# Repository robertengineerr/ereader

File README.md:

# e-reader

An open-source e-reader built on the ESP32-S3. Bare-metal C++ firmware, web-based book management, physical controls. Designed for FOSS developers to build on top of solid hardware.

## Schematic

The full KiCad project is in [`hardware/e_reader_v0.1/`](hardware/e_reader_v0.1/). Pin reference is in [`hardware/connections.md`](hardware/connections.md).

## Hardware

| Component | Part (PCB rev 0.2.0) |
|---|---|
| MCU | ESP32-S3-WROOM-1-N16R8 (16 MB flash, 8 MB octal PSRAM) |
| Display | Waveshare 7.5" V2 e-ink (800×480) via driver HAT on a 9-pin header |
| Storage | microSD (Molex 104031-0811), SPI, FAT32, card detect |
| Input | Alps SKRHABE010 5-way joystick, plus SET / RST / BOOT / RESET buttons |
| Battery | 1-cell protected LiPo via JST-PH, MCP73831 charger, PTC + reverse-polarity FET |
| Power | USB-C (charging + native USB programming), RT9080 3.3 V LDO (~2 µA Iq), slide switch on LDO enable |

The BOM, with an LCSC number for every assembled part, is in
[`hardware/e_reader_v0.1/e_reader_v0.1_bom.csv`](hardware/e_reader_v0.1/e_reader_v0.1_bom.csv).
The design-review log is in [`hardware/REVIEW.md`](hardware/REVIEW.md).

### Wiring

Full pin tables for the breadboard and the PCB are in [`hardware/connections.md`](hardware/connections.md).
The firmware takes its pins from [`src/pins.h`](src/pins.h): the default build uses the breadboard map,
and `pio run -e pcb` uses the PCB map.

The PCB pins that differ from the breadboard are:
| Signal | Breadboard | PCB | Why |
|---|---|---|---|
| Joystick UP / DOWN | GPIO36 / 37 | GPIO4 / 5 | GPIO35–37 are used by the N16R8's octal PSRAM |
| Joystick COM | GPIO35 driven LOW | GND | |
| Display DIN | GPIO46 | GPIO14 | GPIO46 is a boot strapping pin |
| SD card detect | — | GPIO6 | |
| Battery voltage | — | GPIO1 (×2 divider) | |

## Building

1. Install [PlatformIO](https://platformio.org/)
2. Create `src/secrets.h` with your WiFi credentials:
```cpp
#define WIFI_SSID "your-ssid"
#define WIFI_PASS "your-password"
```
3. Build and flash:
```bash
pio run --target upload            # breadboard (DevKitC-1)
pio run -e pcb --target upload     # custom PCB (first time: SW10 ON, hold BOOT, tap RESET; see hardware/connections.md)
```

## Usage

| Button | Library | Reading | Settings |
|---|---|---|---|
| UP | Cursor up | Previous page | Cursor up |
| DOWN | Cursor down | Next page | Cursor down |
| RIGHT | — | Next page | — |
| MID | Select | Back to library | Select |
| LEFT | — | Back to library | Back to library |
| Hold SET at boot | — | — | Enter WiFi mode |

### WiFi Upload

Hold SET while pressing reset, or navigate **Settings → WiFi Upload**. The device connects to your WiFi and shows `ereader.local` on screen. Open `http://ereader.local` in a browser to upload and delete books.

Supported formats (converted to plain text in the browser):
- `.txt` — uploaded directly
- `.epub` — extracted in browser via JSZip
- `.pdf` — extracted via PDF.js
- `.docx` — extracted via JSZip
- `.html` / `.htm` — stripped in browser
- `.fb2` — parsed in browser

Press MID on the device or click **Exit WiFi Mode** in the browser to return to the library.

### Fallback

If no SD card is present the device falls back to a built-in sample text (Iliad Book I, Pope translation) so the UI is always usable.

## Project Structure

```
src/
  main.cpp          # setup, loop, ISR input handling, state machine
  display.cpp/h     # e-ink display abstraction (GxEPD2)
  sd_manager.cpp/h  # SD card init, book listing, pagination engine
  network.cpp/h     # WiFi, HTTP file manager, mDNS
  web_ui.h          # embedded HTML/JS for the browser file manager
  secrets.h         # WiFi credentials (not in repo — create your own)

hardware/
  connections.md              # full pin reference for KiCad
  e_reader_v0.1/              # KiCad project (schematic + PCB)
```

## Roadmap

- [x] Text rendering on e-ink display
- [x] SD card file management
- [x] State machine UI (Library / Reading / Settings)
- [x] WiFi upload with multi-format support
- [x] mDNS (`ereader.local`)
- [x] Hardware schematic v0.1
- [x] Schematic rev 0.2.0: power fixes, 5-way joystick, BOM with LCSC numbers (3 review rounds)
- [x] PCB layout (4-layer, routed, DRC clean) and JLCPCB fab files in `hardware/e_reader_v0.1/fab/`
- [ ] Fabrication and bring-up
- [x] LiPo battery + charging circuit (MCP73831 + RT9080) in schematic
- [ ] Persist reading position (LittleFS)
- [ ] EPUB native rendering
- [ ] 3D printed enclosure

## License

MIT

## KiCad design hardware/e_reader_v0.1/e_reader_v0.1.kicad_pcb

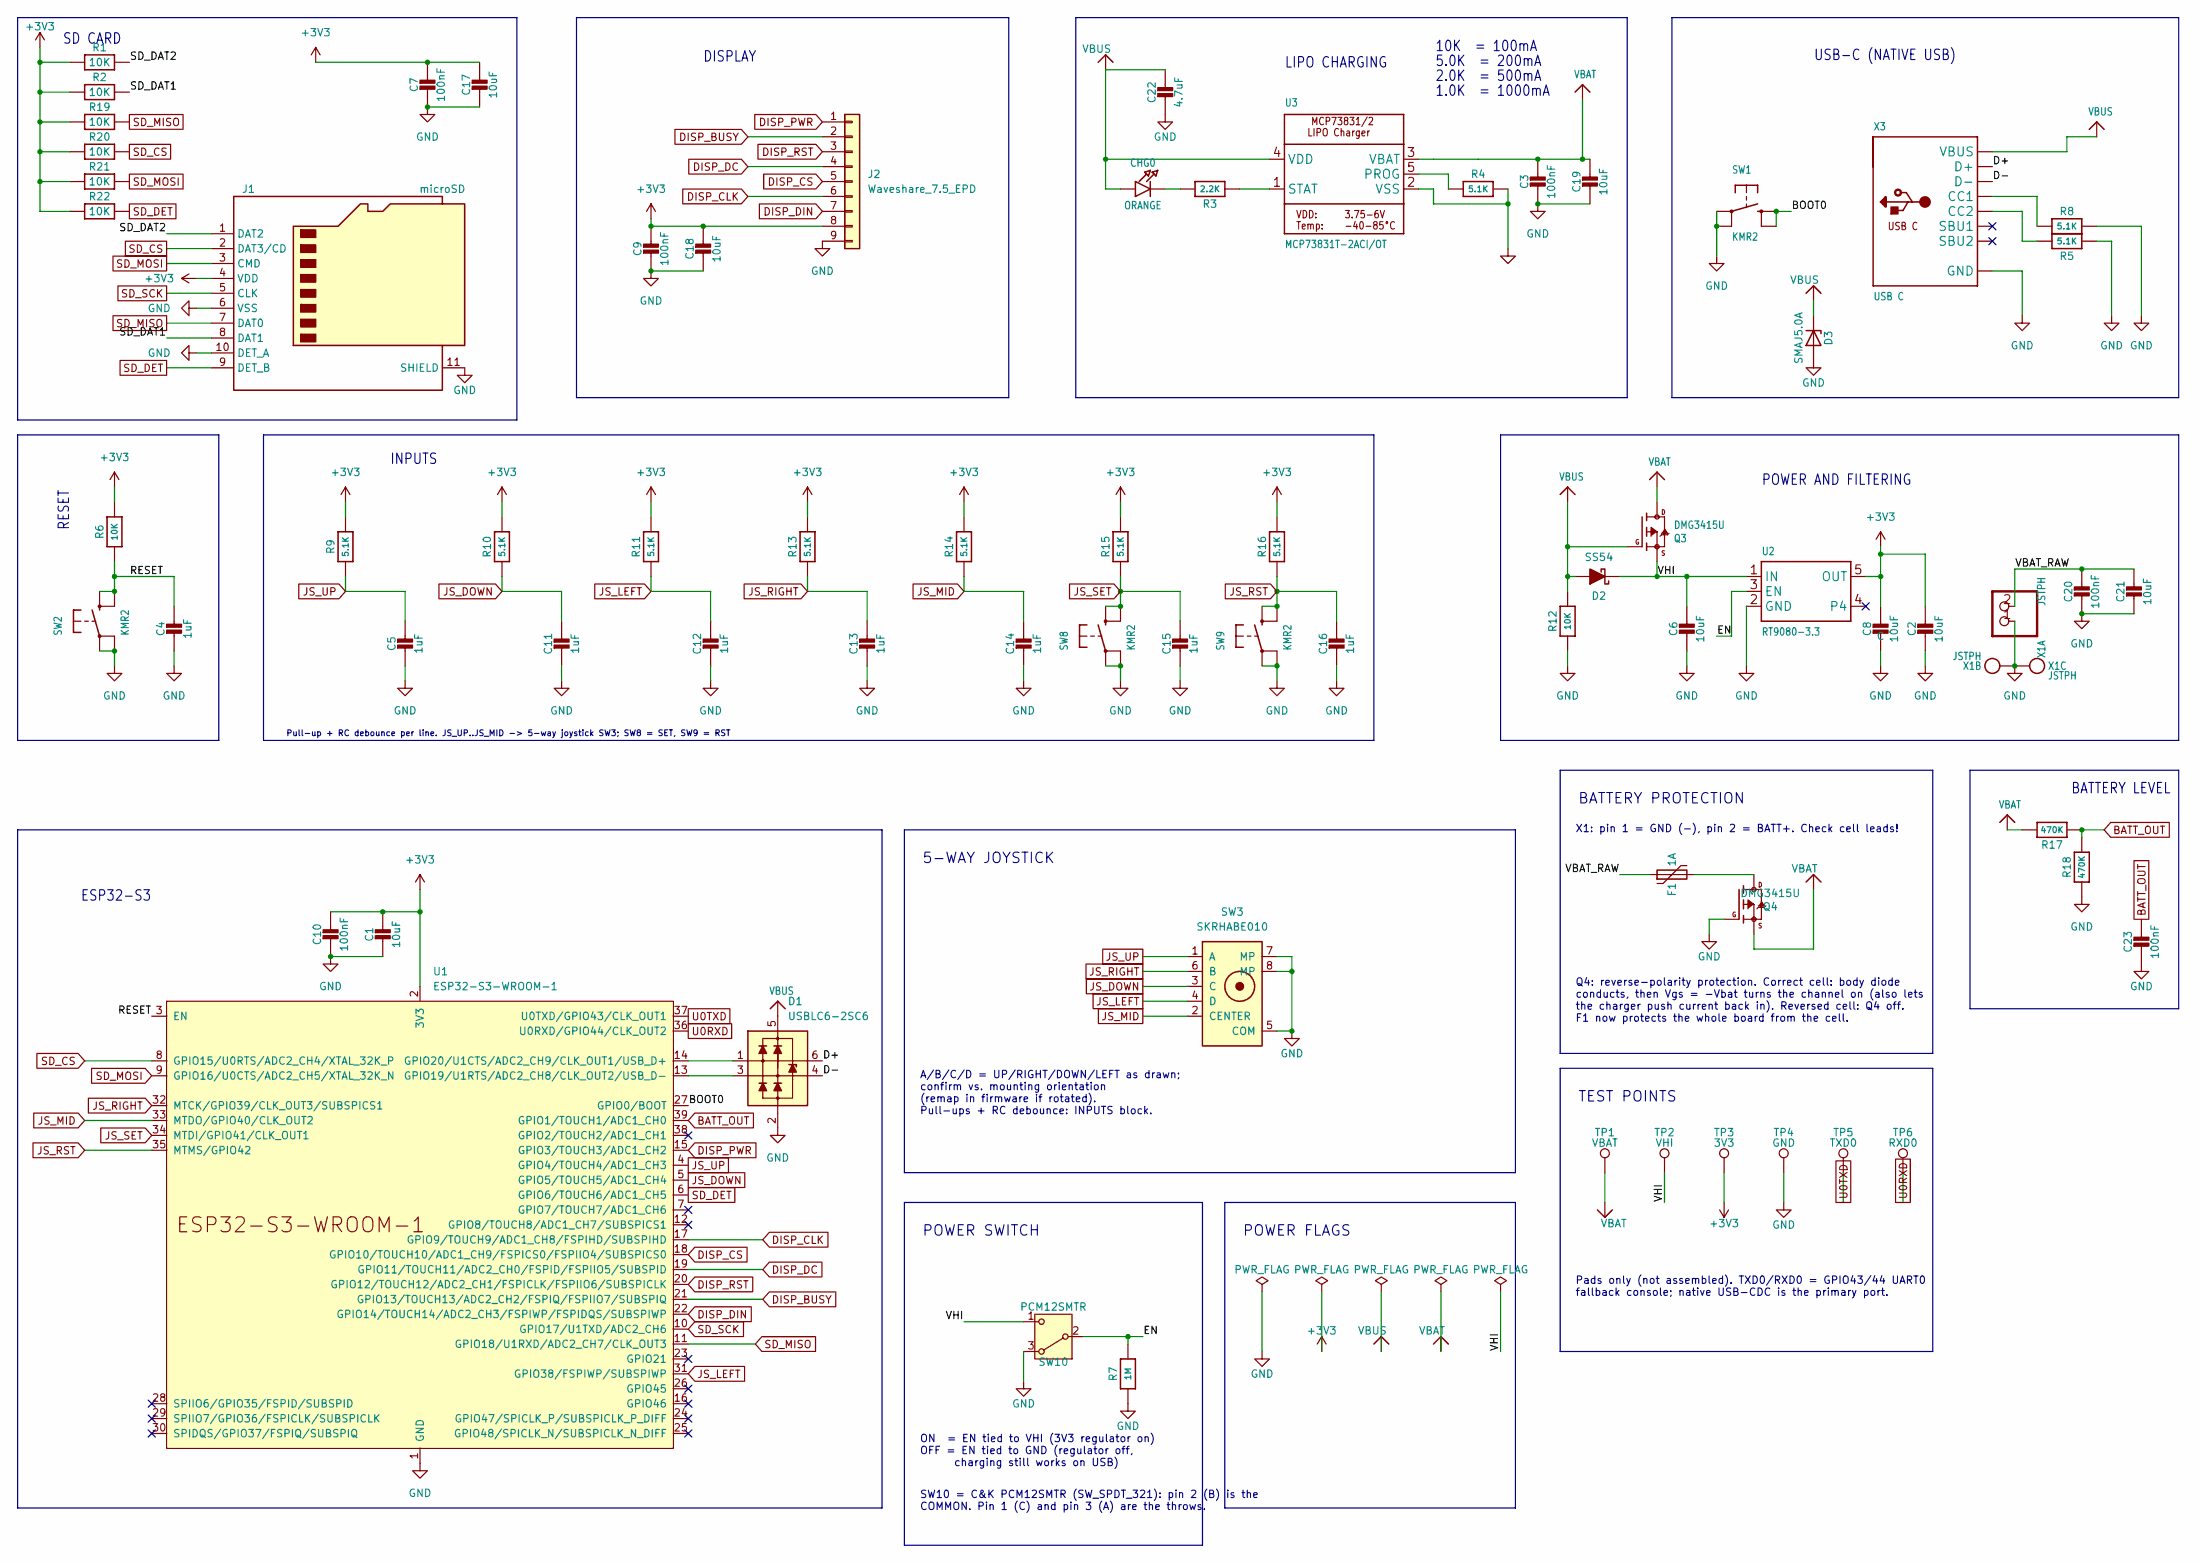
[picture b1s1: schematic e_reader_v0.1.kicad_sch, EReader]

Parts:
C1, C2, C6, C8, C17, C18, C19, C21: 10uF; C_0805_2012Metric; MPN CL21A106KAYNNNE; LCSC C15850
C3, C7, C9, C10, C20, C23: 100nF; C_0402_1005Metric; MPN CL05B104KO5NNNC; LCSC C1525
C4, C5, C11, C12, C13, C14, C15, C16: 1uF; C_0402_1005Metric; MPN CL05A105KA5NQNC; LCSC C52923
C22: 4.7uF; C_0805_2012Metric; MPN CL21A475KAQNNNE; LCSC C1779
CHG0: ORANGE; LED_0603_1608Metric; MPN LITEON LTST-C191KFKT; LCSC C160478
D1: USBLC6-2SC6; SOT-23-6; MPN USBLC6-2SC6; LCSC C7519
D2: SS54; D_SMA; MPN SS54 (SMA); LCSC C22452
D3: SMAJ5.0A; D_SMA; MPN Littelfuse SMAJ5.0A; LCSC C83329
F1: 1A; Fuse_1206_3216Metric; MPN LUTE 1206L100/24NR; LCSC C7542957
J1: microSD; microSD_HC_Molex_104031-0811; MPN Molex 104031-0811; LCSC C585350
J2: Waveshare_7.5_EPD; PinHeader_1x09_P2.54mm_Vertical_SMD_INCP_IPCP254M09PB08S; MPN INCP IPCP254M09PB08S; LCSC C22438433
Q3, Q4: DMG3415U; SOT-23; MPN DMG3415U-7; LCSC C96616
R1, R2, R6, R12, R19, R20, R21, R22: 10K; R_0402_1005Metric; MPN 0402WGF1002TCE; LCSC C25744
R3: 2.2K; R_0402_1005Metric; MPN 0402WGF2201TCE; LCSC C25879
R4, R5, R8, R9, R10, R11, R13, R14, R15, R16: 5.1K; R_0402_1005Metric; MPN 0402WGF5101TCE; LCSC C25905
R7: 1M; R_0402_1005Metric; MPN 0402WGF1004TCE; LCSC C26083
R17, R18: 470K; R_0402_1005Metric; MPN 0402WGF4703TCE; LCSC C25790
SW1, SW2, SW8, SW9: KMR2; SW_Push_1P1T_NO_CK_KMR2; MPN C&K KMR221GLFS; LCSC C72443
SW3: SKRHABE010; SW_Alps_SKRHABE010; MPN Alps SKRHABE010; LCSC C139794
SW10: PCM12SMTR; SW_SPDT_PCM12; MPN C&K PCM12SMTR; LCSC C221841
TP1: VBAT; TestPoint_Pad_D1.5mm
TP2: VHI; TestPoint_Pad_D1.5mm
TP3: 3V3; TestPoint_Pad_D1.5mm
TP4: GND; TestPoint_Pad_D1.5mm
TP5: TXD0; TestPoint_Pad_D1.5mm
TP6: RXD0; TestPoint_Pad_D1.5mm
U1: ESP32-S3-WROOM-1; MPN ESP32-S3-WROOM-1-N16R8; LCSC C2913202
U2: RT9080-3.3; SOT-23-5; MPN RT9080-33GJ5; LCSC C841192
U3: MCP73831T-2ACI/OT; SOT-23-5; MPN MCP73831T-2ACI/OT; LCSC C424093
X1: JSTPH; JST_PH_S2B-PH-SM4-TB_1x02-1MP_P2.00mm_Horizontal; MPN JST S2B-PH-SM4-TB(LF)(SN); LCSC C295747
X3: USB C; USB_C_Receptacle_HRO_TYPE-C-31-M-12; MPN HRO TYPE-C-31-M-12; LCSC C165948

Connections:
+3V3: C1.1, C2.1, C7.1, C8.1, C9.1, C10.1, C17.1, C18.1, J1.4 (VDD), J2.8 (VCC), R1.1, R2.1, R6.2, R9.2, R10.2, R11.2, R13.2, R14.2, R15.2, R16.2, R19.1, R20.1, R21.1, R22.1, TP3.1, U1.2 (3V3), U2.5 (OUT)
/BOOT0: SW1.2 (S), U1.27 (GPIO0/BOOT)
/D+: D1.6 (L1), X3.A6 (D+), X3.B6 (D+)
/D-: D1.4 (L2), X3.A7 (D-), X3.B7 (D-)
/EN: R7.2, SW10.2 (B), U2.3 (EN)
/RESET: C4.1, R6.1, SW2.2 (S), U1.3 (EN)
/SD_DAT1: J1.8 (DAT1), R2.2
/SD_DAT2: J1.1 (DAT2), R1.2
/VBAT_RAW: C20.1, C21.1, F1.1, X1.2
/VHI: C6.1, D2.1 (K), Q3.2 (S), SW10.1 (C), TP2.1, U2.1 (IN)
BATT_OUT: C23.1, R17.1, R18.2, U1.39 (GPIO1/TOUCH1/ADC1_CH0)
DISP_BUSY: J2.2 (BUSY), U1.21 (GPIO13/TOUCH13/ADC2_CH2/FSPIQ/FSPIIO7/S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)
DISP_CLK: J2.6 (CLK), U1.17 (GPIO9/TOUCH9/ADC1_CH8/FSPIHD/SUBSPIHD)
DISP_CS: J2.5 (CS), U1.18 (GPIO10/TOUCH10/ADC1_CH9/FSPICS0/FSPIIO4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)
DISP_DC: J2.4 (DC), U1.19 (GPIO11/TOUCH11/ADC2_CH0/FSPID/FSPIIO5/S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)
DISP_DIN: J2.7 (DIN), U1.22 (GPIO14/TOUCH14/ADC2_CH3/FSPIWP/FSPIDQS/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)
DISP_PWR: J2.1 (PWR), U1.15 (GPIO3/TOUCH3/ADC1_CH2)
DISP_RST: J2.3 (RST), U1.20 (GPIO12/TOUCH12/ADC2_CH1/FSPICLK/FSPIIO6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)
GND: C1.2, C2.2, C3.2, C4.2, C5.2, C6.2, C7.2, C8.2, C9.2, C10.2, C11.2, C12.2, C13.2, C14.2, C15.2, C16.2, C17.2, C18.2, C19.2, C20.2, C21.2, C22.2, C23.2, D1.2 (VN), D3.2 (A), J1.6 (VSS), J1.10 (DET_A), J1.11 (SHIELD), J2.9 (GND), Q4.1 (G), R4.2, R5.1, R7.1, R8.2, R12.1, R18.1, SW1.1, SW2.1, SW3.5 (COM), SW3.7 (MP), SW3.8 (MP), SW8.1, SW9.1, SW10.3 (A), TP4.1, U1.1 (GND), U1.40 (GND), U1.41 (GND), U2.2 (GND), U3.2 (VSS), X1.1, X1.MP, X3.A1 (GND), X3.A12 (GND), X3.B1 (GND), X3.B12 (GND), X3.S1 (GND)
JS_DOWN: C11.1, R10.1, SW3.3 (C), U1.5 (GPIO5/TOUCH5/ADC1_CH4)
JS_LEFT: C12.1, R11.1, SW3.4 (D), U1.31 (GPIO38/FSPIWP/SUBSPIWP)
JS_MID: C14.1, R14.1, SW3.2 (CENTER), U1.33 (MTDO/GPIO40/CLK_OUT2)
JS_RIGHT: C13.1, R13.1, SW3.6 (B), U1.32 (MTCK/GPIO39/CLK_OUT3/SUBSPICS1)
JS_RST: C16.1, R16.1, SW9.2 (S), U1.35 (MTMS/GPIO42)
JS_SET: C15.1, R15.1, SW8.2 (S), U1.34 (MTDI/GPIO41/CLK_OUT1)
JS_UP: C5.1, R9.1, SW3.1 (A), U1.4 (GPIO4/TOUCH4/ADC1_CH3)
unnamed: CHG0.1 (C), R3.2
unnamed: F1.2, Q4.3 (D)
unnamed: D1.3 (L2), U1.13 (GPIO19/U1RTS/ADC2_CH8/CLK_OUT2/USB_D-)
unnamed: D1.1 (L1), U1.14 (GPIO20/U1CTS/ADC2_CH9/CLK_OUT1/USB_D+)
unnamed: R4.1, U3.5 (PROG)
unnamed: R3.1, U3.1 (STAT)
unnamed: R8.1, X3.A5 (CC1)
unnamed: R5.2, X3.B5 (CC2)
SD_CS: J1.2 (DAT3/CD), R20.2, U1.8 (GPIO15/U0RTS/ADC2_CH4/XTAL_32K_P)
SD_DET: J1.9 (DET_B), R22.2, U1.6 (GPIO6/TOUCH6/ADC1_CH5)
SD_MISO: J1.7 (DAT0), R19.2, U1.11 (GPIO18/U1RXD/ADC2_CH7/CLK_OUT3)
SD_MOSI: J1.3 (CMD), R21.2, U1.9 (GPIO16/U0CTS/ADC2_CH5/XTAL_32K_N)
SD_SCK: J1.5 (CLK), U1.10 (GPIO17/U1TXD/ADC2_CH6)
U0RXD: TP6.1, U1.36 (U0RXD/GPIO44/CLK_OUT2)
U0TXD: TP5.1, U1.37 (U0TXD/GPIO43/CLK_OUT1)
VBAT: C3.1, C19.1, Q3.3 (D), Q4.2 (S), R17.2, TP1.1, U3.3 (VBAT)
VBUS: C22.1, CHG0.2 (A), D1.5 (VP), D2.2 (A), D3.1 (K), Q3.1 (G), R12.2, U3.4 (VDD), X3.A4 (VBUS), X3.A9 (VBUS), X3.B4 (VBUS), X3.B9 (VBUS)

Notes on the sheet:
INPUTS
LIPO CHARGING
5.0K = 200mA
ESP32-S3
USB-C (NATIVE USB)
RESET
SD CARD
1.0K = 1000mA
10K = 100mA
DISPLAY
2.0K = 500mA
POWER AND FILTERING
BATTERY LEVEL
POWER SWITCH
ON = EN tied to VHI (3V3 regulator on) OFF = EN tied to GND (regulator off, charging still works on USB)
5-WAY JOYSTICK
A/B/C/D = UP/RIGHT/DOWN/LEFT as drawn; confirm vs. mounting orientation (remap in firmware if rotated). Pull-ups + RC debounce: INPUTS block.
Pull-up + RC debounce per line. JS_UP..JS_MID -> 5-way joystick SW3; SW8 = SET, SW9 = RST
POWER FLAGS
BATTERY PROTECTION
Q4: reverse-polarity protection. Correct cell: body diode conducts, then Vgs = -Vbat turns the channel on (also lets the charger push current back in). Reversed cell: Q4 off. F1 now protects the whole board from the cell.
SW10 = C&K PCM12SMTR (SW_SPDT_321): pin 2 (B) is the COMMON. Pin 1 (C) and pin 3 (A) are the throws.
TEST POINTS
Pads only (not assembled). TXD0/RXD0 = GPIO43/44 UART0 fallback console; native USB-CDC is the primary port.
X1: pin 1 = GND (-), pin 2 = BATT+. Check cell leads!

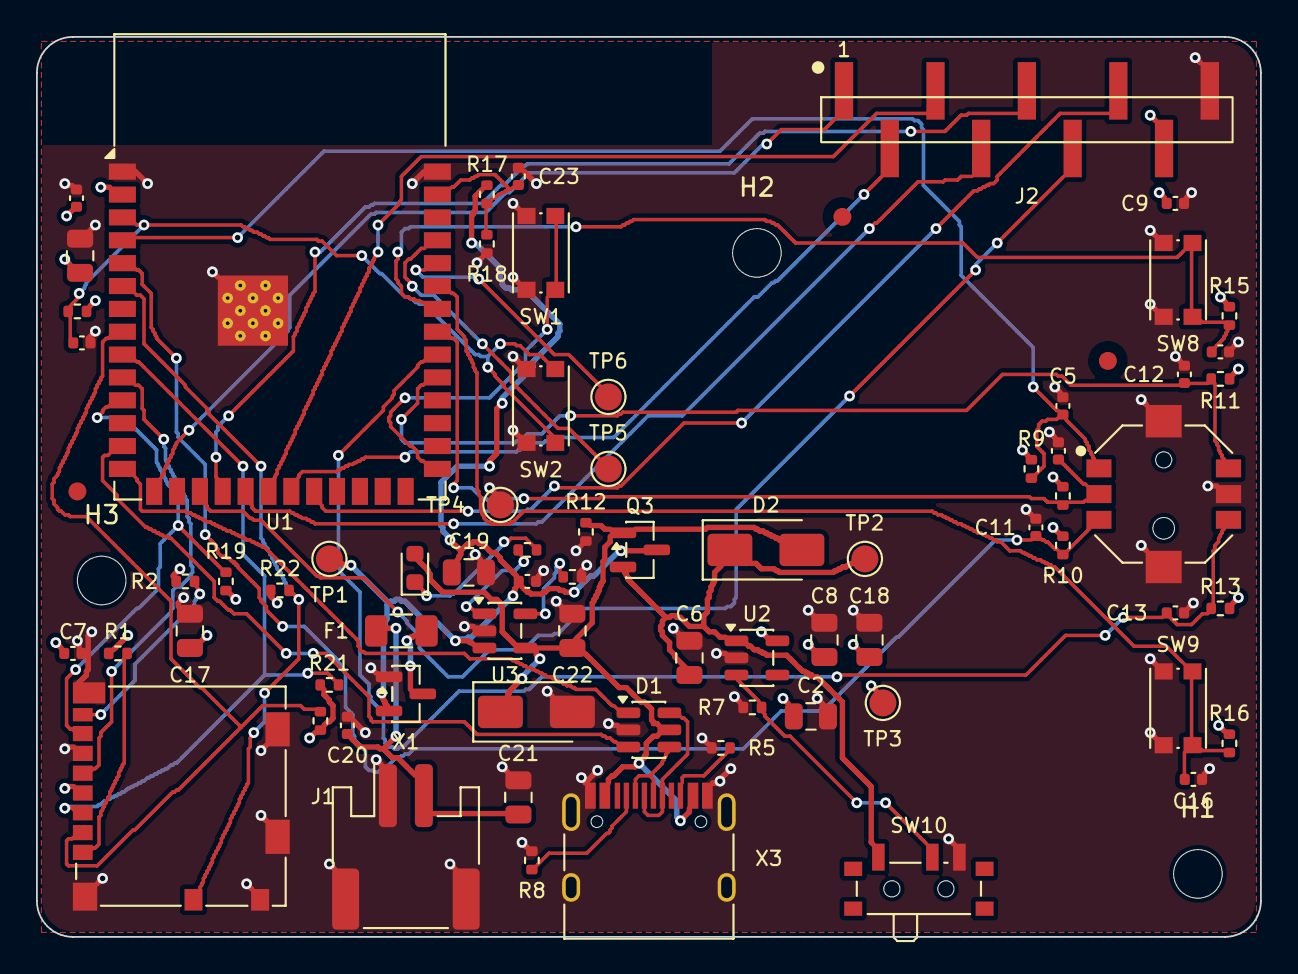
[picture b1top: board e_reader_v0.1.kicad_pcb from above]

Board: 4 copper layers, 68.0 x 50.0 mm, 77 parts (0 on the bottom side), 43 nets.

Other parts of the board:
FID1, FID2, FID3: Fiducial_1mm_Mask2mm
H1, H2, H3: MountingHole_2.7mm_M2.5

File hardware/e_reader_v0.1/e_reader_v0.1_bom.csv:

"Reference","Value","Footprint","MPN","LCSC","QUANTITY"
"C1,C2,C6,C8,C17-C19,C21","10uF","Capacitor_SMD:C_0805_2012Metric","CL21A106KAYNNNE","C15850","8"
"C3,C7,C9,C10,C20,C23","100nF","Capacitor_SMD:C_0402_1005Metric","CL05B104KO5NNNC","C1525","6"
"C4,C5,C11-C16","1uF","Capacitor_SMD:C_0402_1005Metric","CL05A105KA5NQNC","C52923","8"
"C22","4.7uF","Capacitor_SMD:C_0805_2012Metric","CL21A475KAQNNNE","C1779","1"
"CHG0","ORANGE","LED_SMD:LED_0603_1608Metric","LITEON LTST-C191KFKT","C160478","1"
"D1","USBLC6-2SC6","Package_TO_SOT_SMD:SOT-23-6","USBLC6-2SC6","C7519","1"
"D2","SS54","Diode_SMD:D_SMA","SS54 (SMA)","C22452","1"
"D3","SMAJ5.0A","Diode_SMD:D_SMA","Littelfuse SMAJ5.0A","C83329","1"
"F1","1A","Fuse:Fuse_1206_3216Metric","LUTE 1206L100/24NR","C7542957","1"
"J1","microSD","Connector_Card:microSD_HC_Molex_104031-0811","Molex 104031-0811","C585350","1"
"J2","Waveshare_7.5_EPD","ereader:PinHeader_1x09_P2.54mm_Vertical_SMD_INCP_IPCP254M09PB08S","INCP IPCP254M09PB08S","C22438433","1"
"Q3,Q4","DMG3415U","Package_TO_SOT_SMD:SOT-23","DMG3415U-7","C96616","2"
"R1,R2,R6,R12,R19-R22","10K","Resistor_SMD:R_0402_1005Metric","0402WGF1002TCE","C25744","8"
"R3","2.2K","Resistor_SMD:R_0402_1005Metric","0402WGF2201TCE","C25879","1"
"R4,R5,R8-R11,R13-R16","5.1K","Resistor_SMD:R_0402_1005Metric","0402WGF5101TCE","C25905","10"
"R7","1M","Resistor_SMD:R_0402_1005Metric","0402WGF1004TCE","C26083","1"
"R17,R18","470K","Resistor_SMD:R_0402_1005Metric","0402WGF4703TCE","C25790","2"
"SW1,SW2,SW8,SW9","KMR2","Button_Switch_SMD:SW_Push_1P1T_NO_CK_KMR2","C&K KMR221GLFS","C72443","4"
"SW3","SKRHABE010","ereader:SW_Alps_SKRHABE010","Alps SKRHABE010","C139794","1"
"SW10","PCM12SMTR","Button_Switch_SMD:SW_SPDT_PCM12","C&K PCM12SMTR","C221841","1"
"U1","ESP32-S3-WROOM-1","RF_Module:ESP32-S3-WROOM-1","ESP32-S3-WROOM-1-N16R8","C2913202","1"
"U2","RT9080-3.3","Package_TO_SOT_SMD:SOT-23-5","RT9080-33GJ5","C841192","1"
"U3","MCP73831T-2ACI/OT","Package_TO_SOT_SMD:SOT-23-5","MCP73831T-2ACI/OT","C424093","1"
"X1","JSTPH","Connector_JST:JST_PH_S2B-PH-SM4-TB_1x02-1MP_P2.00mm_Horizontal","JST S2B-PH-SM4-TB(LF)(SN)","C295747","1"
"X3","USB C","Connector_USB:USB_C_Receptacle_HRO_TYPE-C-31-M-12","HRO TYPE-C-31-M-12","C165948","1"

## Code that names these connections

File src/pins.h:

#pragma once
// Pin map for both hardware targets.
//   default        : breadboard (ESP32-S3-DevKitC-1, joystick module COM driven by a GPIO)
//   -DBOARD_PCB    : e_reader_v0.1 PCB (hardware/e_reader_v0.1/e_reader_v0.1.kicad_sch, rev 0.2.0)
//
// PCB notes:
//  * GPIO35-37 are wired to the octal PSRAM inside ESP32-S3-WROOM-1-N16R8, so the
//    PCB moves JOY_UP/JOY_DWN to GPIO4/GPIO5.
//  * GPIO46 is a boot strapping pin, so the PCB moves EPD_DIN to GPIO14.
//  * The joystick COM pin is tied straight to GND (no JOY_COM GPIO).
//  * Every input has a 5.1K pull-up + 1uF RC on the board; INPUT_PULLUP is harmless.

// --- e-paper (FSPI) ---
#define EPD_PWR    3
#define EPD_BUSY  13
#define EPD_RST   12
#define EPD_DC    11
#define EPD_CS    10
#define EPD_CLK    9

// --- SD card (HSPI) ---
#define SD_CS    15
#define SD_MOSI  16
#define SD_SCK   17
#define SD_MISO  18

#ifdef BOARD_PCB
  #define EPD_DIN   14
  #define JOY_COM   -1   // tied to GND on the PCB
  #define JOY_UP     4
  #define JOY_DWN    5
  #define SD_DET     6   // card-detect switch to GND (use INPUT_PULLUP)
  #define BATT_ADC   1   // VBAT via 470K/470K divider + 100nF -> multiply reading by 2
#else
  #define EPD_DIN   46
  #define JOY_COM   35   // driven OUTPUT LOW as a virtual GND on the breadboard
  #define JOY_UP    36
  #define JOY_DWN   37
  #define SD_DET    -1
  #define BATT_ADC  -1
#endif

#define JOY_LFT  38
#define JOY_RHT  39
#define JOY_MID  40
#define JOY_SET  41  // hold at boot to enter WiFi upload mode
#define JOY_RST  42

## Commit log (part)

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2026-03-09 Update .gitignore for KiCad temp files and book files
